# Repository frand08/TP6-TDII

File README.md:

# TP6-TDII
Realización del TP6 (placa en kicad)

Integrantes: Dominguez, Francisco
             Sivinian, Juan

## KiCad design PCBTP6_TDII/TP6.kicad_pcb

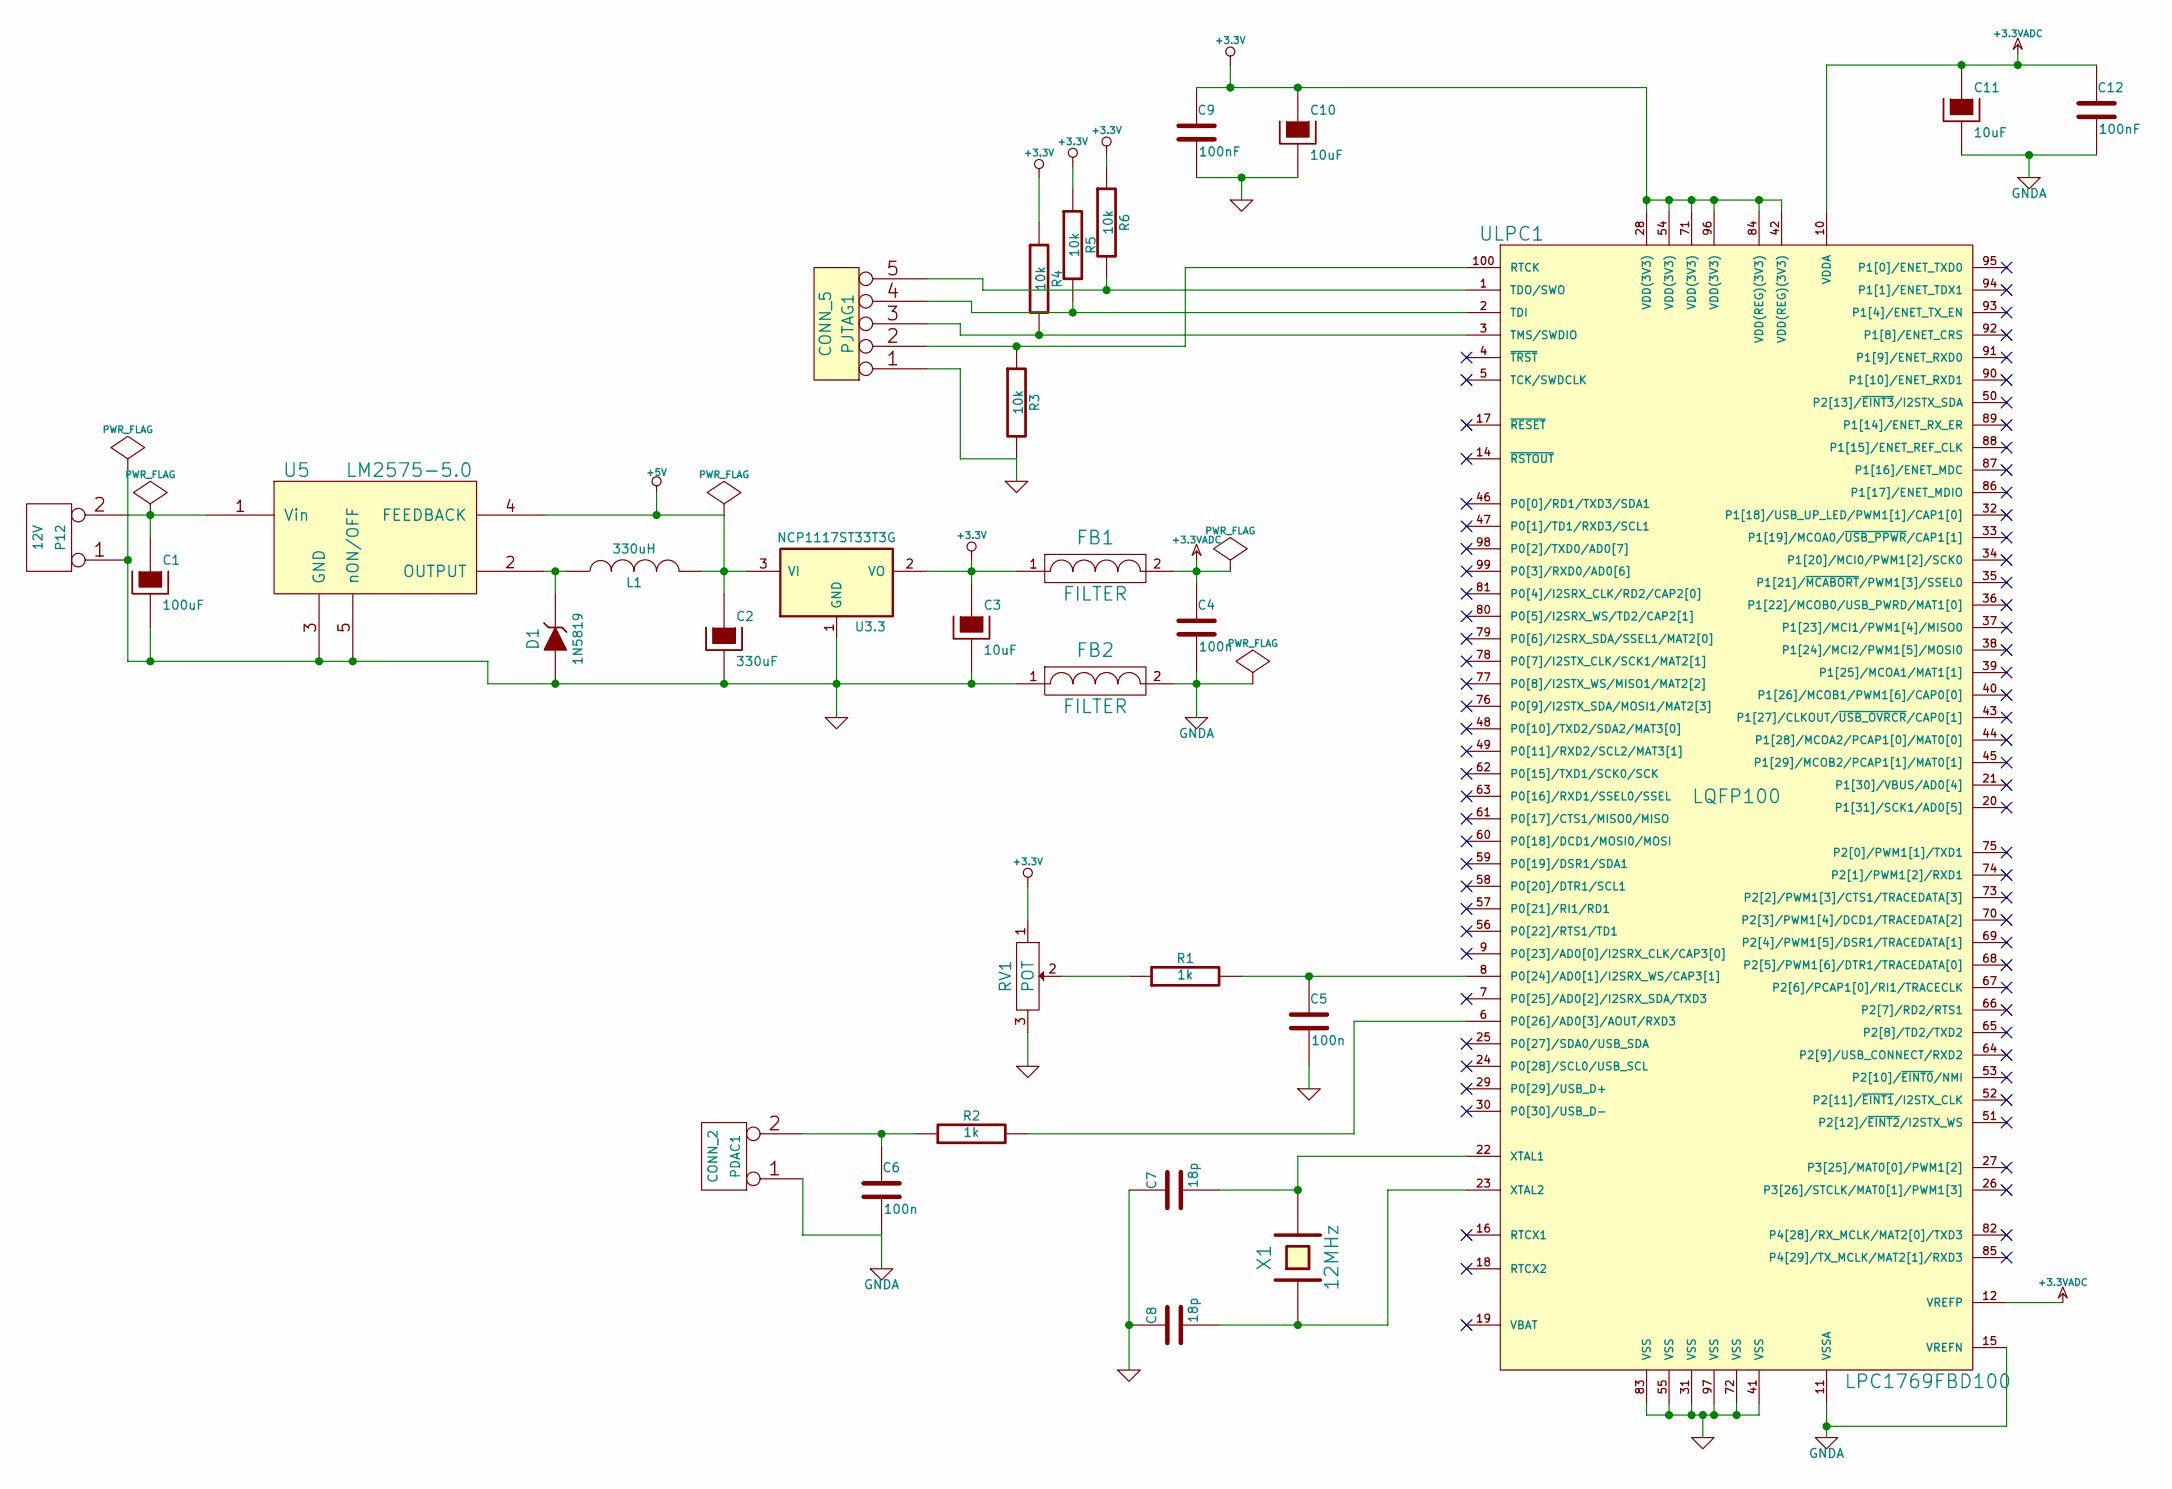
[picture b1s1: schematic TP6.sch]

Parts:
C1: 100uF
C2: 330uF
C3, C10, C11: 10uF
C4, C5, C6: 100n
C7, C8: 18p
C9, C12: 100nF
D1: 1N5819
FB1, FB2: FILTER
L1: 330uH
P12: 12V
PDAC1: CONN_2
PJTAG1: CONN_5
R1, R2: 1k
R3, R4, R5, R6: 10k
RV1: POT
U3.3: NCP1117ST33T3G
U5: LM2575-5.0
ULPC1: LPC1769FBD100; LQFP100
X1: 12MHz

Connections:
+3.3V: C3.1, C9.1, C10.1, FB1.1, R4.1, R5.1, R6.1, RV1.1, U3.3.2 (VO), ULPC1.28 (VDD(3V3)), ULPC1.42 (VDD(REG)(3V3)), ULPC1.54 (VDD(3V3)), ULPC1.71 (VDD(3V3)), ULPC1.84 (VDD(REG)(3V3)), ULPC1.96 (VDD(3V3))
+3.3VADC: C4.1, C11.1, C12.1, FB1.2, ULPC1.10 (VDDA), ULPC1.12 (VREFP)
+5V: C2.1, L1.2, U3.3.3 (VI), U5.4 (FEEDBACK)
GND: C1.2, C2.2, C3.2, C5.2, C7.1, C8.1, C9.2, C10.2, D1.1 (A), FB2.1, P12.1, PJTAG1.1, R3.2, RV1.3, U3.3.1 (GND), U5.3 (GND), U5.5 (nON/OFF), ULPC1.31 (VSS), ULPC1.41 (VSS), ULPC1.55 (VSS), ULPC1.72 (VSS), ULPC1.83 (VSS), ULPC1.97 (VSS)
GNDA: C4.2, C6.2, C11.2, C12.2, FB2.2, PDAC1.1, ULPC1.11 (VSSA), ULPC1.15 (VREFN)
unnamed: C6.1, PDAC1.2 (PM), R2.1
unnamed: R2.2, ULPC1.6 (P0[26]/AD0[3]/AOUT/RXD3)
unnamed: PJTAG1.4, R5.2, ULPC1.2 (TDI)
unnamed: PJTAG1.2, R3.1, ULPC1.100 (RTCK)
unnamed: PJTAG1.3, R4.2, ULPC1.3 (TMS/SWDIO)
unnamed: PJTAG1.5, R6.2, ULPC1.1 (TDO/SWO)
unnamed: C1.1, P12.2 (PM), U5.1 (Vin)
unnamed: D1.2 (K), L1.1, U5.2 (OUTPUT)
unnamed: C7.2, ULPC1.22 (XTAL1), X1.2
unnamed: R1.1, RV1.2
unnamed: C8.2, ULPC1.23 (XTAL2), X1.1
unnamed: C5.1, R1.2, ULPC1.8 (P0[24]/AD0[1]/I2SRX_WS/CAP3[1])

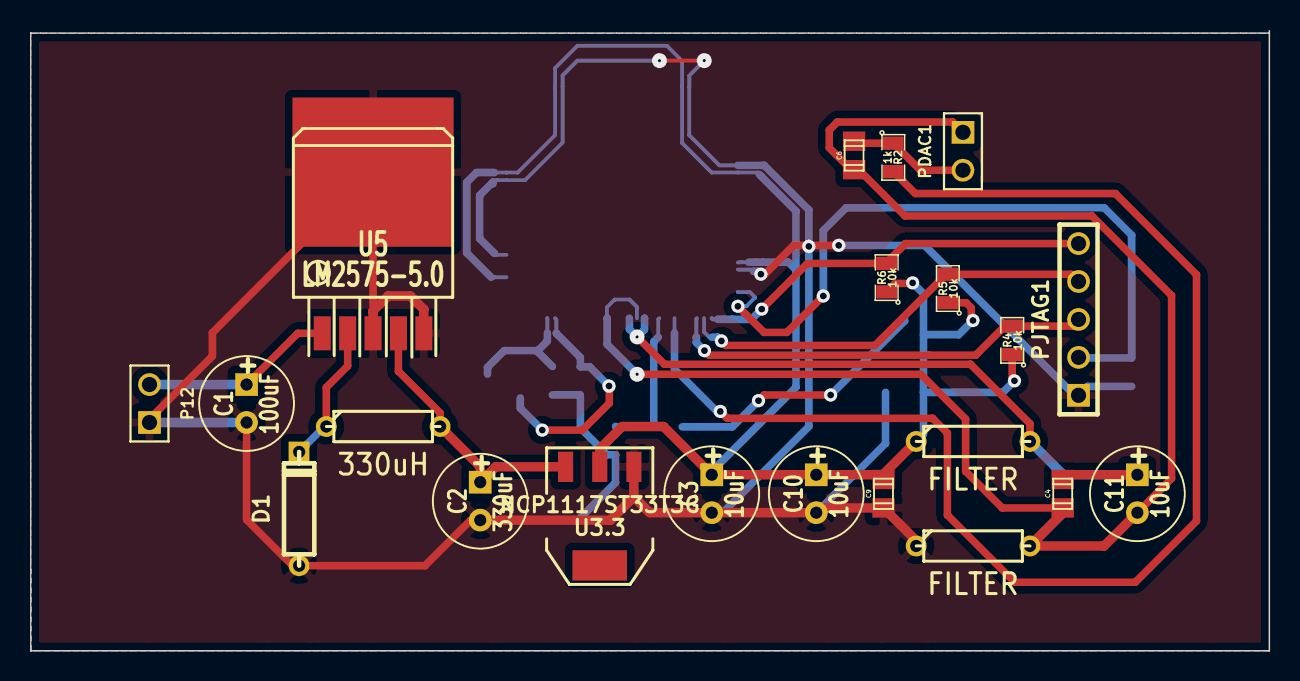
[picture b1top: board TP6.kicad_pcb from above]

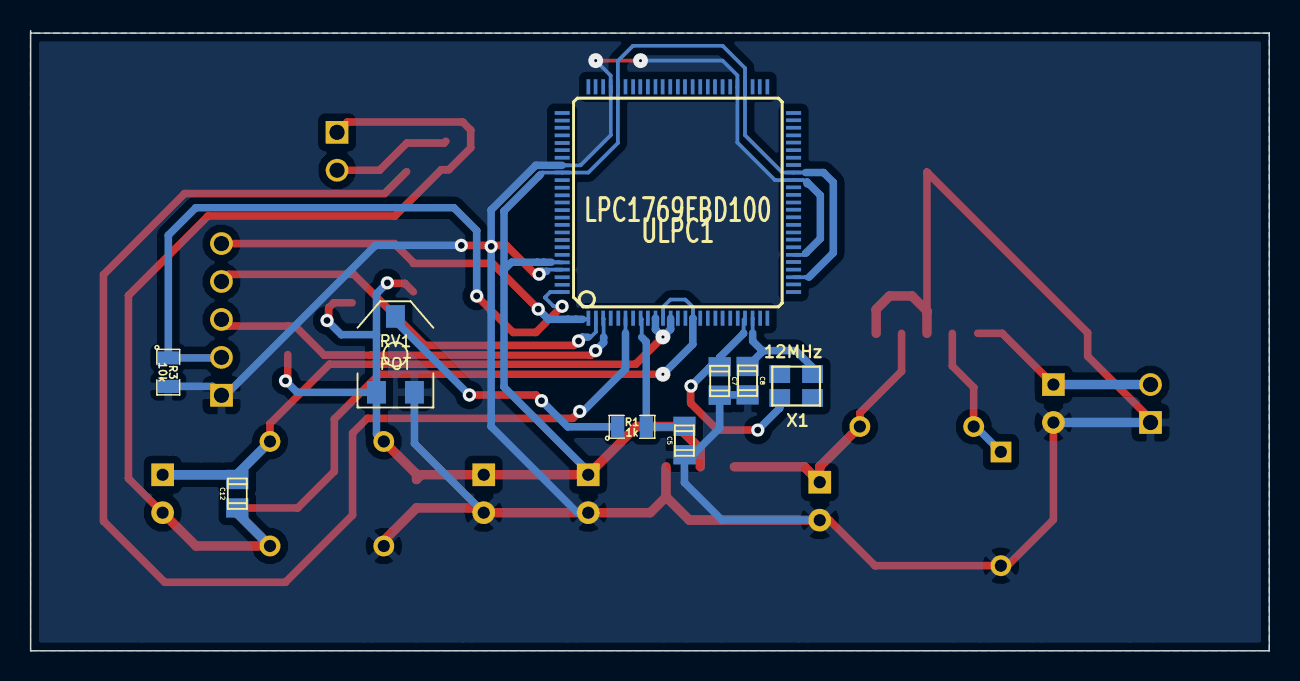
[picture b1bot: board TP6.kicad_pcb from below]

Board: 2 copper layers, 83.0 x 41.5 mm, 30 parts (9 on the bottom side), 17 nets.

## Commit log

2015-09-14 Falta hacer el pcb, tanto acomodar los componentes como rootearlo
2015-09-28 Terminado el pcb
